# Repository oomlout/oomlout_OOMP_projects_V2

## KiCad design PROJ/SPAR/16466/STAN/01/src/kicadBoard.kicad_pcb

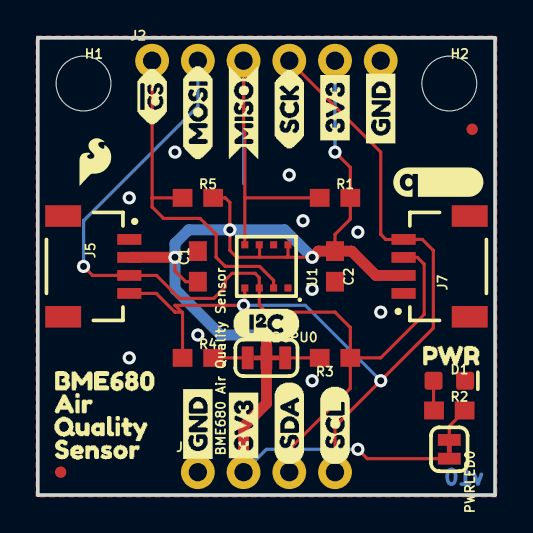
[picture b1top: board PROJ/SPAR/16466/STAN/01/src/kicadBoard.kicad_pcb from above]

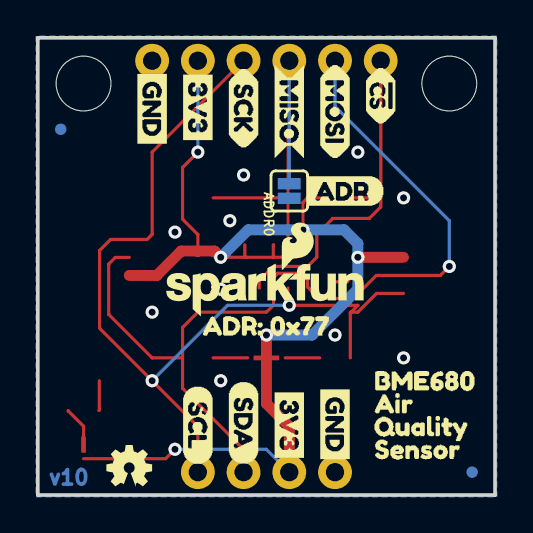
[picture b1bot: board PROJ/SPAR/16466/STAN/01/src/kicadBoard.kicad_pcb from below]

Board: 2 copper layers, 25.4 x 25.4 mm, 60 parts (21 on the bottom side), 10 nets.

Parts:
ADDR0: JUMPER-SMT_2_NO_SILK; SMT-JUMPER_2_NO_SILK
C1, C2: 0.1uF; 0603
D1: RED; LED-0603
FD1, FD2, FD3, FD4: FIDUCIALUFIDUCIAL; FIDUCIAL-MICRO
FRAME1: FRAME-LETTER; CREATIVE_COMMONS
H1, H2: STAND-OFFTIGHT; STAND-OFF-TIGHT
I2CPU0: I2C PU; SMT-JUMPER_3_2-NC_TRACE_SILK
J1: I2C; 1X04_NO_SILK
J2: SPI; 1X06_NO_SILK
J5, J7: QWIIC; JST04_1MM_RA
LOGO1: OSHW-LOGOMINI; OSHW-LOGO-MINI
LOGO2: SFE_LOGO_NAME_FLAME.1_INCH; SFE_LOGO_NAME_FLAME_.1
LOGO3: REVISION
LOGO4: SFE_LOGO_FLAME.1_INCH; SFE_LOGO_FLAME_.1
PWRLED0: JUMPER-SMT_2_NC_TRACE_SILK; SMT-JUMPER_2_NC_TRACE_SILK
R1, R3, R4, R5: 4.7k; 0603@1
R2: 1k; 0603
U1: BME680 Air Quality Sensor; LGA3.0X3.0
U$1, U$2: MISO_O
U$3, U$4: !CS_I
U$5, U$6: MOSI_I
U$7, U$8: SCK_I
U$9, U$10, U$16, U$17: 3V3_P
U$11, U$12, U$13, U$14: GND_P
U$15: I2C
U$18, U$19: SDA_IO
U$20, U$21: SCL_IO
U$22, U$26: BME6800
U$23, U$27: AIR1
U$24, U$28: QUALITY2
U$25, U$29: SENSOR3
U$30: ADR4
U$32: QWIIC_5MM
U$33: ADR#_0X770
U$34: PWR_TO

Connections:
3.3V: C1.1, C2.1, I2CPU0.2, J1.2, J2.5, J5.2, J7.2, PWRLED0.2, R1.2, R5.2, U1.6, U1.8
GND: ADDR0.1, C1.2, C2.2, D1.C, J1.1, J2.6, J5.1, J7.1, U1.1, U1.7
unnamed: PWRLED0.1, R2.2
unnamed: D1.A, R2.1
unnamed: I2CPU0.3, R3.2
unnamed: I2CPU0.1, R4.2
SCK/SCL: J1.4, J2.4, J5.4, J7.4, R4.1, U1.4
SDI/SDA: J1.3, J2.2, J5.3, J7.3, R3.1, U1.3
SDO/ADR: ADDR0.2, J2.3, R1.1, U1.5
~CS: J2.1, R5.1, U1.2

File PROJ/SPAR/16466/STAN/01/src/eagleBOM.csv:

"Part";"Value";"Device";"Package";"Description";"DESIGNER";"PROD_ID";"REV";"VALUE";
"ADDR";"JUMPER-SMT_2_NO_SILK";"JUMPER-SMT_2_NO_SILK";"SMT-JUMPER_2_NO_SILK";"Normally open jumper";"";"";"";"";
"C1";"0.1uF";"0.1UF-0603-100V-10%";"0603";"0.1µF ceramic capacitors";"";"CAP-08390";"";"0.1uF";
"C2";"0.1uF";"0.1UF-0603-100V-10%";"0603";"0.1µF ceramic capacitors";"";"CAP-08390";"";"0.1uF";
"D1";"RED";"LED-RED0603";"LED-0603";"Red SMD LED";"";"DIO-00819";"";"RED";
"FD1";"FIDUCIALUFIDUCIAL";"FIDUCIALUFIDUCIAL";"FIDUCIAL-MICRO";"Fiducial Alignment Points";"";"";"";"";
"FD2";"FIDUCIALUFIDUCIAL";"FIDUCIALUFIDUCIAL";"FIDUCIAL-MICRO";"Fiducial Alignment Points";"";"";"";"";
"FD3";"FIDUCIALUFIDUCIAL";"FIDUCIALUFIDUCIAL";"FIDUCIAL-MICRO";"Fiducial Alignment Points";"";"";"";"";
"FD4";"FIDUCIALUFIDUCIAL";"FIDUCIALUFIDUCIAL";"FIDUCIAL-MICRO";"Fiducial Alignment Points";"";"";"";"";
"FRAME1";"FRAME-LETTER";"FRAME-LETTER";"CREATIVE_COMMONS";"Schematic Frame - Letter";"";"";"";"";
"H1";"STAND-OFFTIGHT";"STAND-OFFTIGHT";"STAND-OFF-TIGHT";"Stand Off";"";"";"";"";
"H2";"STAND-OFFTIGHT";"STAND-OFFTIGHT";"STAND-OFF-TIGHT";"Stand Off";"";"";"";"";
"I2CPU";"I2C PU";"JUMPER-SMT_3_2-NC_TRACE_SILK";"SMT-JUMPER_3_2-NC_TRACE_SILK";"Normally closed trace jumper (2 of 2 connections)";"";"";"";"";
"J1";"I2C";"CONN_041X04_NO_SILK";"1X04_NO_SILK";"Multi connection point. Often used as Generic Header-pin footprint for 0.1 inch spaced/style header connections";"";"CONN-09696";"";"";
"J2";"SPI";"CONN_06NO_SILK_FEMALE_PTH";"1X06_NO_SILK";"Multi connection point. Often used as Generic Header-pin footprint for 0.1 inch spaced/style header connections";"";"CONN-08437";"";"";
"J5";"QWIIC";"QWIIC_CONNECTORJS-1MM";"JST04_1MM_RA";"SparkFun I2C Standard Qwiic Connector";"";"CONN-13694";"";"QWIIC_RIGHT_ANGLE";
"J7";"QWIIC";"QWIIC_CONNECTORJS-1MM";"JST04_1MM_RA";"SparkFun I2C Standard Qwiic Connector";"";"CONN-13694";"";"QWIIC_RIGHT_ANGLE";
"LOGO1";"OSHW-LOGOMINI";"OSHW-LOGOMINI";"OSHW-LOGO-MINI";"Open-Source Hardware (OSHW) Logo";"";"";"";"";
"LOGO2";"SFE_LOGO_NAME_FLAME.1_INCH";"SFE_LOGO_NAME_FLAME.1_INCH";"SFE_LOGO_NAME_FLAME_.1";"SparkFun Font Logo w/ Flame";"";"";"";"";
"LOGO3";"REVISION";"REVISION";"REVISION";""Revision By" Text";"";"";"";"";
"LOGO4";"SFE_LOGO_FLAME.1_INCH";"SFE_LOGO_FLAME.1_INCH";"SFE_LOGO_FLAME_.1";"SparkFun Flame Logo";"";"";"";"";
"PWRLED";"JUMPER-SMT_2_NC_TRACE_SILK";"JUMPER-SMT_2_NC_TRACE_SILK";"SMT-JUMPER_2_NC_TRACE_SILK";"Normally closed trace jumper";"";"";"";"";
"R1";"4.7k";"4.7KOHM-0603-1/10W-1%";"0603@1";"4.7kΩ resistor";"";"RES-07857";"";"4.7k";
"R2";"1k";"1KOHM-0603-1/10W-1%";"0603";"1kΩ resistor";"";"RES-07856";"";"1k";
"R3";"4.7k";"4.7KOHM-0603-1/10W-1%";"0603@1";"4.7kΩ resistor";"";"RES-07857";"";"4.7k";
"R4";"4.7k";"4.7KOHM-0603-1/10W-1%";"0603@1";"4.7kΩ resistor";"";"RES-07857";"";"4.7k";
"R5";"4.7k";"4.7KOHM-0603-1/10W-1%";"0603@1";"4.7kΩ resistor";"";"RES-07857";"";"4.7k";
"U1";"BME680 Air Quality Sensor";"BME680-LGA";"LGA3.0X3.0";"Bosch BME680 &ndash; Combined Humidity and Pressure Sensor";"";"IC-14656";"";"BME680";

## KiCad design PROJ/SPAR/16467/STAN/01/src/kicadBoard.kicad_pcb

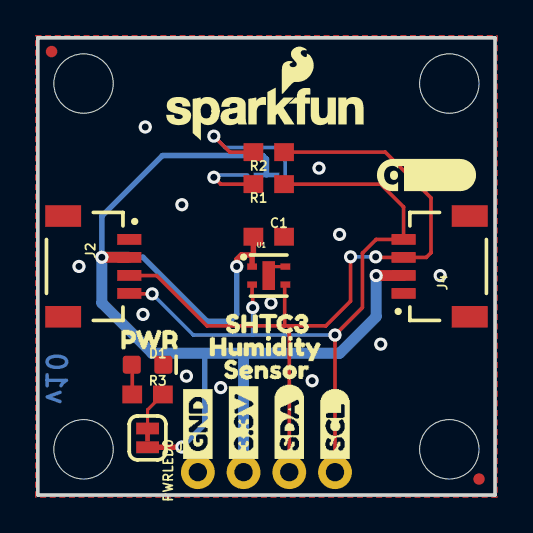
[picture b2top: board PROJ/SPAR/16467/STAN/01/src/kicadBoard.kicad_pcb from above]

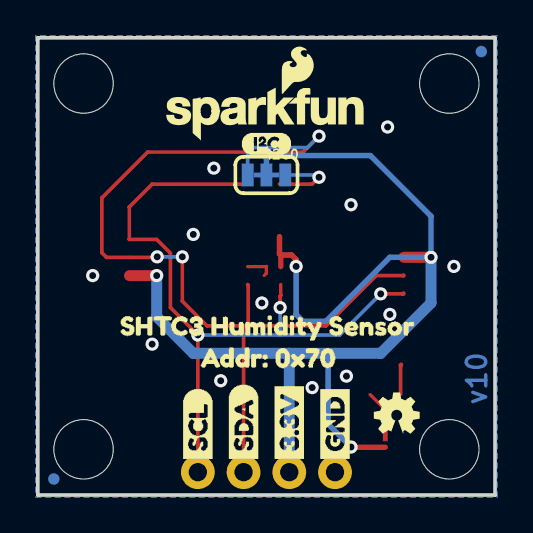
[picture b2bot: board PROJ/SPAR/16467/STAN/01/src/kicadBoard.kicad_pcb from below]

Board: 2 copper layers, 25.4 x 25.4 mm, 40 parts (12 on the bottom side), 8 nets.

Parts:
C1: 0.1uF; 0603
D1: RED; LED-0603
FRAME1: FRAME-LETTER; CREATIVE_COMMONS
I2C0: JUMPER-SMT_3_2-NC_TRACE_SILK; SMT-JUMPER_3_2-NC_TRACE_SILK
J1: 1X04_NO_SILK
J2, J4: QWIIC_RIGHT_ANGLE; JST04_1MM_RA
JP1, JP2, JP5, JP6: FIDUCIALUFIDUCIAL; MICRO-FIDUCIAL
JP3, JP4, JP7, JP8: STAND-OFF
LOGO1: OSHW-LOGOMINI; OSHW-LOGO-MINI
LOGO2, LOGO3: SFE_LOGO_NAME_FLAME.1_INCH; SFE_LOGO_NAME_FLAME_.1
LOGO4: REVISION
PWRLED0: JUMPER-SMT_2_NC_TRACE_SILK; SMT-JUMPER_2_NC_TRACE_SILK
R1, R2: 2.2k; 0603
R3: 1k; 0603
U1: SHTC3
U$1: ADDR#_0X700
U$2: PWR_TO
U$3, U$22: GND1
U$4, U$21: 3#3V2
U$5, U$27: SDA8
U$6, U$26: SCL9
U$7: SHTC3_HUMIDITY_SENSOR2
U$8: _SHTC31
U$9: I_SUPER2_C-()-03
U$10: HUMIDITY2
U$11: QWIIC_5.5MM
U$12: SENSOR0

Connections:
3.3V: C1.1, I2C0.2, J1.2, J2.2, J4.2, PWRLED0.2, U1.1
GND: C1.2, D1.C, J1.1, J2.1, J4.1, U1.4, U1.5
unnamed: I2C0.3, R1.2
unnamed: I2C0.1, R2.2
unnamed: D1.A, R3.1
unnamed: PWRLED0.1, R3.2
SCL: J1.4, J2.4, J4.4, R1.1, U1.2
SDA: J1.3, J2.3, J4.3, R2.1, U1.3

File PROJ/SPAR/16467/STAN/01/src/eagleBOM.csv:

"Part";"Value";"Device";"Package";"Description";"DESIGNER";"PROD_ID";"REV";"VALUE";
"C1";"0.1uF";"0.1UF-0603-25V-(+80/-20%)";"0603";"0.1µF ceramic capacitors";"";"CAP-00810";"";"0.1uF";
"D1";"RED";"LED-RED0603";"LED-0603";"Red SMD LED";"";"DIO-00819";"";"RED";
"FRAME1";"FRAME-LETTER";"FRAME-LETTER";"CREATIVE_COMMONS";"Schematic Frame - Letter";"";"";"";"";
"I2C";"JUMPER-SMT_3_2-NC_TRACE_SILK";"JUMPER-SMT_3_2-NC_TRACE_SILK";"SMT-JUMPER_3_2-NC_TRACE_SILK";"Normally closed trace jumper (2 of 2 connections)";"";"";"";"";
"J1";"";"CONN_041X04_NO_SILK";"1X04_NO_SILK";"Multi connection point. Often used as Generic Header-pin footprint for 0.1 inch spaced/style header connections";"";"CONN-09696";"";"";
"J2";"QWIIC_RIGHT_ANGLE";"QWIIC_CONNECTORJS-1MM";"JST04_1MM_RA";"SparkFun I2C Standard Qwiic Connector";"";"CONN-13694";"";"QWIIC_RIGHT_ANGLE";
"J4";"QWIIC_RIGHT_ANGLE";"QWIIC_CONNECTORJS-1MM";"JST04_1MM_RA";"SparkFun I2C Standard Qwiic Connector";"";"CONN-13694";"";"QWIIC_RIGHT_ANGLE";
"JP1";"FIDUCIALUFIDUCIAL";"FIDUCIALUFIDUCIAL";"MICRO-FIDUCIAL";"Fiducial Alignment Points";"";"";"";"";
"JP2";"FIDUCIALUFIDUCIAL";"FIDUCIALUFIDUCIAL";"MICRO-FIDUCIAL";"Fiducial Alignment Points";"";"";"";"";
"JP3";"STAND-OFF";"STAND-OFF";"STAND-OFF";"Stand Off";"";"";"";"";
"JP4";"STAND-OFF";"STAND-OFF";"STAND-OFF";"Stand Off";"";"";"";"";
"JP5";"FIDUCIALUFIDUCIAL";"FIDUCIALUFIDUCIAL";"MICRO-FIDUCIAL";"Fiducial Alignment Points";"";"";"";"";
"JP6";"FIDUCIALUFIDUCIAL";"FIDUCIALUFIDUCIAL";"MICRO-FIDUCIAL";"Fiducial Alignment Points";"";"";"";"";
"JP7";"STAND-OFF";"STAND-OFF";"STAND-OFF";"Stand Off";"";"";"";"";
"JP8";"STAND-OFF";"STAND-OFF";"STAND-OFF";"Stand Off";"";"";"";"";
"LOGO1";"OSHW-LOGOMINI";"OSHW-LOGOMINI";"OSHW-LOGO-MINI";"Open-Source Hardware (OSHW) Logo";"";"";"";"";
"LOGO2";"SFE_LOGO_NAME_FLAME.1_INCH";"SFE_LOGO_NAME_FLAME.1_INCH";"SFE_LOGO_NAME_FLAME_.1";"SparkFun Font Logo w/ Flame";"";"";"";"";
"LOGO3";"SFE_LOGO_NAME_FLAME.1_INCH";"SFE_LOGO_NAME_FLAME.1_INCH";"SFE_LOGO_NAME_FLAME_.1";"SparkFun Font Logo w/ Flame";"";"";"";"";
"LOGO4";"REVISION";"REVISION";"REVISION";""Revision By" Text";"";"";"";"";
"PWRLED";"JUMPER-SMT_2_NC_TRACE_SILK";"JUMPER-SMT_2_NC_TRACE_SILK";"SMT-JUMPER_2_NC_TRACE_SILK";"Normally closed trace jumper";"";"";"";"";
"R1";"2.2k";"2.2KOHM-0603-1/10W-1%";"0603";"2.2kΩ resistor";"";"RES-08272";"";"2.2k";
"R2";"2.2k";"2.2KOHM-0603-1/10W-1%";"0603";"2.2kΩ resistor";"";"RES-08272";"";"2.2k";
"R3";"1k";"1KOHM-0603-1/10W-1%";"0603";"1kΩ resistor";"";"RES-07856";"";"1k";
"U1";"SHTC3";"SHTC3";"SHTC3";"Sensirion SHTC3 Humidity Sensor";"";"IC-14840";"";"SHTC3";

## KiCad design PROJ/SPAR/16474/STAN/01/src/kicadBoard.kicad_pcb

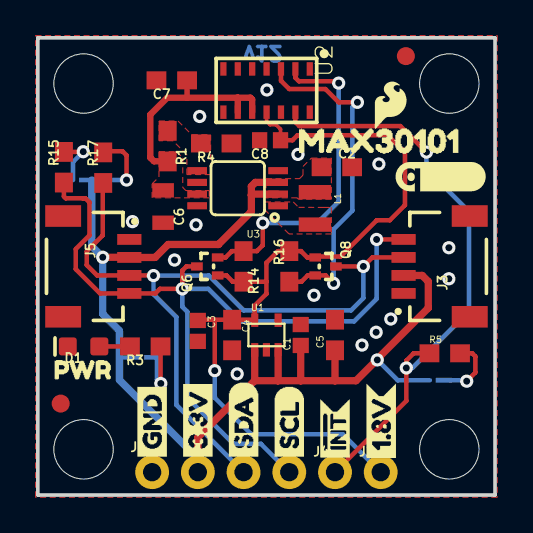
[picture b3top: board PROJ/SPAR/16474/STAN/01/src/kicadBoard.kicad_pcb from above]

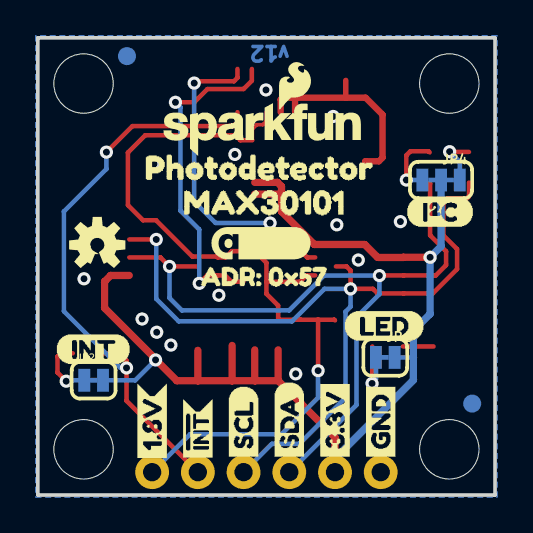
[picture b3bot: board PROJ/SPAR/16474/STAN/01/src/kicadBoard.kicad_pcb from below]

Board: 2 copper layers, 25.4 x 25.4 mm, 65 parts (20 on the bottom side), 16 nets.

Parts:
C1, C3, C8: 0.1uF; 0402
C2, C4, C5, C7: 10uF; 0603
C6: 22uF; 0805
D1: RED; LED-0603
FID1, FID2, FID3, FID4: FIDUCIAL1X2; FIDUCIAL-1X2
FRAME1: FRAME-LETTER; CREATIVE_COMMONS
J1: PTH; 1X04_NO_SILK
J2, J4: 1X01_NO_SILK
J3, J5: QWIIC_RA; JST04_1MM_RA
JP1: LED; SMT-JUMPER_2_NC_TRACE_SILK
JP2: INT; SMT-JUMPER_2_NC_TRACE_SILK
JP4: I2C PU; SMT-JUMPER_3_2-NC_TRACE_SILK
L1: 2.2μH; 0806
LOGO1: SFE_LOGO_NAME_FLAME.1_INCH; SFE_LOGO_NAME_FLAME_.1
LOGO2: OSHW-LOGOS; OSHW-LOGO-S
LOGO3: QWIIC_LOGO_5MM; QWIIC_5MM
LOGO4: SFE_LOGO_FLAME.1_INCH; SFE_LOGO_FLAME_.1
Q6, Q8: 20V/0.2A/8MHz/1.2Ω/1Vth; SOT-416FL
R1: 750K; 0603
R3: 1k; 0603
R4: 100k; 0603
R5: 4.7k; 0603
R14, R15, R16, R17: 2.2k; 0603
STANDOFF1, STANDOFF2, STANDOFF3, STANDOFF4: STAND-OFF
U1: 1.8V/100mA; SC70
U2: MAX30101EFD; 14_PIN_OESIP
U3: PAM2401; MSOP8
U$1: PHOTODETECTOR3
U$3, U$11: INT#-[_-04
U$4, U$24: MAX301010
U$7: INT-()-04
U$8: LED0
U$9, U$12: SCL-[)
U$10, U$23: GND-04
U$13, U$14: SDA-[)
U$15: ADR#_0X570
U$16: QWIIC_5.5MM
U$19, U$22: 3.3V
U$20, U$27: 1#8V0
U$21: I_SUPER2_C-()-04
U$26: PWR_TO

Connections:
1.8V: C3.1, C4.1, C8.1, J2.1, Q6.1, Q8.1, R14.2, R16.2, U1.5, U2.P11
3.3V: C1.1, C2.1, C5.1, J1.2, J3.2, J5.2, JP1.2, JP2.2, JP4.2, L1.1, U1.1, U1.3, U3.2, U3.3
5V: C6.1, C7.1, R1.2, U2.P9, U2.P10, U3.7
GND: C1.2, C2.2, C3.2, C4.2, C5.2, C6.2, C7.2, C8.2, D1.C, J1.1, J3.1, J5.1, R4.1, U1.2, U1.4, U2.P4, U2.P12, U3.4, U3.8
LV_SCL: Q6.2, R14.1, U2.P2
LV_SDA: Q8.2, R16.1, U2.P3
unnamed: JP2.1, R5.2
unnamed: R1.1, R4.2, U3.5
unnamed: L1.2, U3.1
unnamed: D1.A, R3.2
unnamed: JP4.3, R15.2
unnamed: JP4.1, R17.2
unnamed: JP1.1, R3.1
SCL: J1.4, J3.4, J5.4, Q6.3, R15.1
SDA: J1.3, J3.3, J5.3, Q8.3, R17.1
~INT: J4.1, R5.1, U2.P13

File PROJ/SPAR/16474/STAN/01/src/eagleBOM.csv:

"Part";"Value";"Device";"Package";"Description";"DESIGNER";"PROD_ID";"REV";"VALUE";
"C1";"0.1uF";"0.1UF-0402-16V-10%";"0402";"0.1µF ceramic capacitors";"";"CAP-12416";"";"0.1uF";
"C2";"10uF";"10UF-0603-6.3V-20%";"0603";"10.0µF ceramic capacitors";"";"CAP-11015";"";"10uF";
"C3";"0.1uF";"0.1UF-0402-16V-10%";"0402";"0.1µF ceramic capacitors";"";"CAP-12416";"";"0.1uF";
"C4";"10uF";"10UF-0603-6.3V-20%";"0603";"10.0µF ceramic capacitors";"";"CAP-11015";"";"10uF";
"C5";"10uF";"10UF-0603-6.3V-20%";"0603";"10.0µF ceramic capacitors";"";"CAP-11015";"";"10uF";
"C6";"22uF";"22UF-0805-6.3V-20%";"0805";"22µF ceramic capacitors";"";"CAP-08402";"";"22uF";
"C7";"10uF";"10UF-0603-6.3V-20%";"0603";"10.0µF ceramic capacitors";"";"CAP-11015";"";"10uF";
"C8";"0.1uF";"0.1UF-0402-16V-10%";"0402";"0.1µF ceramic capacitors";"";"CAP-12416";"";"0.1uF";
"D1";"RED";"LED-RED0603";"LED-0603";"Red SMD LED";"";"DIO-00819";"";"RED";
"FID1";"FIDUCIAL1X2";"FIDUCIAL1X2";"FIDUCIAL-1X2";"Fiducial Alignment Points";"";"";"";"";
"FID2";"FIDUCIAL1X2";"FIDUCIAL1X2";"FIDUCIAL-1X2";"Fiducial Alignment Points";"";"";"";"";
"FID3";"FIDUCIAL1X2";"FIDUCIAL1X2";"FIDUCIAL-1X2";"Fiducial Alignment Points";"";"";"";"";
"FID4";"FIDUCIAL1X2";"FIDUCIAL1X2";"FIDUCIAL-1X2";"Fiducial Alignment Points";"";"";"";"";
"FRAME1";"FRAME-LETTER";"FRAME-LETTER";"CREATIVE_COMMONS";"Schematic Frame - Letter";"";"";"";"";
"J1";"PTH";"I2C_STANDARD_NO_SILK";"1X04_NO_SILK";"SparkFun I2C Standard Pinout Header";"";"";"";"";
"J2";"";"CONN_01PTH_NO_SILK_YES_STOP";"1X01_NO_SILK";"Single connection point. Often used as Generic Header-pin footprint for 0.1 inch spaced/style header connections";"";"";"";"";
"J3";"QWIIC_RA";"QWIIC_CONNECTORJS-1MM";"JST04_1MM_RA";"SparkFun I2C Standard Qwiic Connector";"";"CONN-13694";"";"QWIIC_RIGHT_ANGLE";
"J4";"";"CONN_01PTH_NO_SILK_YES_STOP";"1X01_NO_SILK";"Single connection point. Often used as Generic Header-pin footprint for 0.1 inch spaced/style header connections";"";"";"";"";
"J5";"QWIIC_RA";"QWIIC_CONNECTORJS-1MM";"JST04_1MM_RA";"SparkFun I2C Standard Qwiic Connector";"";"CONN-13694";"";"QWIIC_RIGHT_ANGLE";
"JP1";"LED";"JUMPER-SMT_2_NC_TRACE_SILK";"SMT-JUMPER_2_NC_TRACE_SILK";"Normally closed trace jumper";"";"";"";"";
"JP2";"INT";"JUMPER-SMT_2_NC_TRACE_SILK";"SMT-JUMPER_2_NC_TRACE_SILK";"Normally closed trace jumper";"";"";"";"";
"JP4";"I2C PU";"JUMPER-SMT_3_2-NC_TRACE_SILK";"SMT-JUMPER_3_2-NC_TRACE_SILK";"Normally closed trace jumper (2 of 2 connections)";"";"";"";"";
"L1";"2.2μH";"2.2μH_SHIELDED_INDUCTOR";"0806";"Murata 2.2uH Inductor";"";"NDUC-14257";"";"";
"LOGO1";"SFE_LOGO_NAME_FLAME.1_INCH";"SFE_LOGO_NAME_FLAME.1_INCH";"SFE_LOGO_NAME_FLAME_.1";"SparkFun Font Logo w/ Flame";"";"";"";"";
"LOGO2";"OSHW-LOGOS";"OSHW-LOGOS";"OSHW-LOGO-S";"Open-Source Hardware (OSHW) Logo";"";"";"";"";
"LOGO3";"QWIIC_LOGO_5MM";"QWIIC_LOGO_5MM";"QWIIC_5MM";"Qwiic Logos for placement on schematic and PCB. The 5.5mm silk logo is best for placing next to Qwiic connector.";"";"";"";"";
"LOGO4";"SFE_LOGO_FLAME.1_INCH";"SFE_LOGO_FLAME.1_INCH";"SFE_LOGO_FLAME_.1";"SparkFun Flame Logo";"";"";"";"";
"Q6";"20V/0.2A/8MHz/1.2Ω/1Vth";"MOSFET-NCH-RE1C00UNTL";"SOT-416FL";"N-channel MOSFETs";"";"TRANS-14399";"";"20V/0.2A/8MHz/1.2Ω/1Vth";
"Q8";"20V/0.2A/8MHz/1.2Ω/1Vth";"MOSFET-NCH-RE1C00UNTL";"SOT-416FL";"N-channel MOSFETs";"";"TRANS-14399";"";"20V/0.2A/8MHz/1.2Ω/1Vth";
"R1";"750K";"750KOHM-0603-1/10W-1%";"0603";"750Ω resistor";"";"RES-13768";"";"750K";
"R3";"1k";"1KOHM-0603-1/10W-1%";"0603";"1kΩ resistor";"";"RES-07856";"";"1k";
"R4";"100k";"100KOHM-0603-1/10W-1%";"0603";"100kΩ resistor";"";"RES-07828";"";"100k";
"R5";"4.7k";"4.7KOHM-0603-1/10W-1%";"0603";"4.7kΩ resistor";"";"RES-07857";"";"4.7k";
"R14";"2.2k";"2.2KOHM-0603-1/10W-1%";"0603";"2.2kΩ resistor";"";"RES-08272";"";"2.2k";
"R15";"2.2k";"2.2KOHM-0603-1/10W-1%";"0603";"2.2kΩ resistor";"";"RES-08272";"";"2.2k";
"R16";"2.2k";"2.2KOHM-0603-1/10W-1%";"0603";"2.2kΩ resistor";"";"RES-08272";"";"2.2k";
"R17";"2.2k";"2.2KOHM-0603-1/10W-1%";"0603";"2.2kΩ resistor";"";"RES-08272";"";"2.2k";
"STANDOFF1";"STAND-OFF";"STAND-OFF";"STAND-OFF";"#4 Stand Off";"";"";"";"";
"STANDOFF2";"STAND-OFF";"STAND-OFF";"STAND-OFF";"#4 Stand Off";"";"";"";"";
"STANDOFF3";"STAND-OFF";"STAND-OFF";"STAND-OFF";"#4 Stand Off";"";"";"";"";
"STANDOFF4";"STAND-OFF";"STAND-OFF";"STAND-OFF";"#4 Stand Off";"";"";"";"";
"U1";"1.8V/100mA";"V_REG_SP62141.8V";"SC70";"";"";"VREG-08428";"";"1.8V/100mA";
"U2";"MAX30101EFD";"MAX30101EFD";"14_PIN_OESIP";"MAX30101 High-Sensitivity Pulse Oximeter and";"";"IC-14270";"";"";
"U3";"PAM2401";"PAM2401";"MSOP8";"PAM2401 - Boost PMIC";"";"IC-13769";"";"PAM2401";

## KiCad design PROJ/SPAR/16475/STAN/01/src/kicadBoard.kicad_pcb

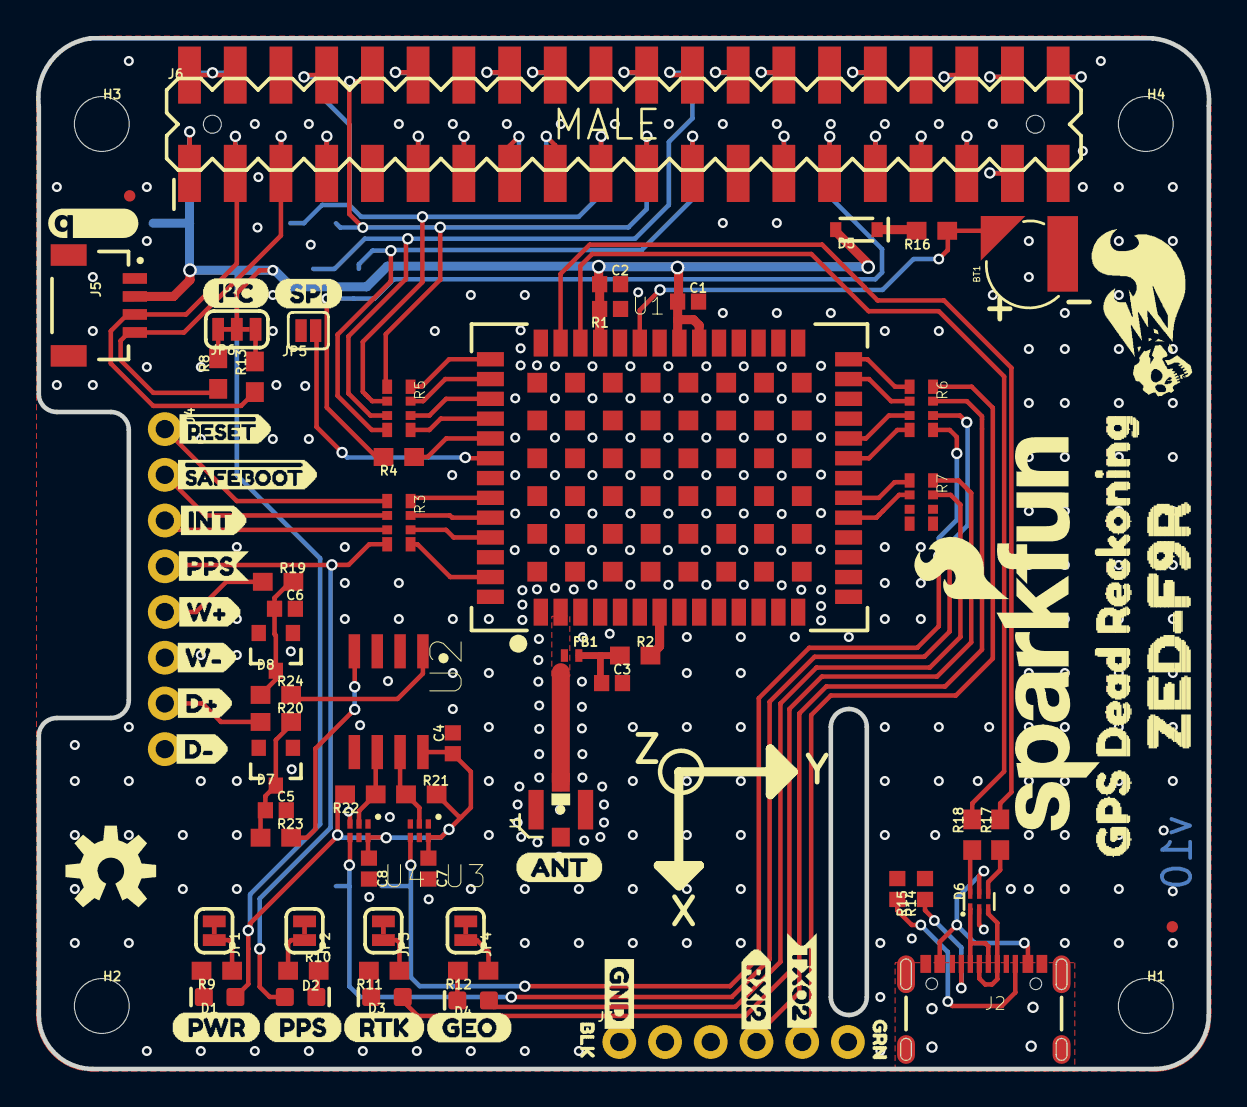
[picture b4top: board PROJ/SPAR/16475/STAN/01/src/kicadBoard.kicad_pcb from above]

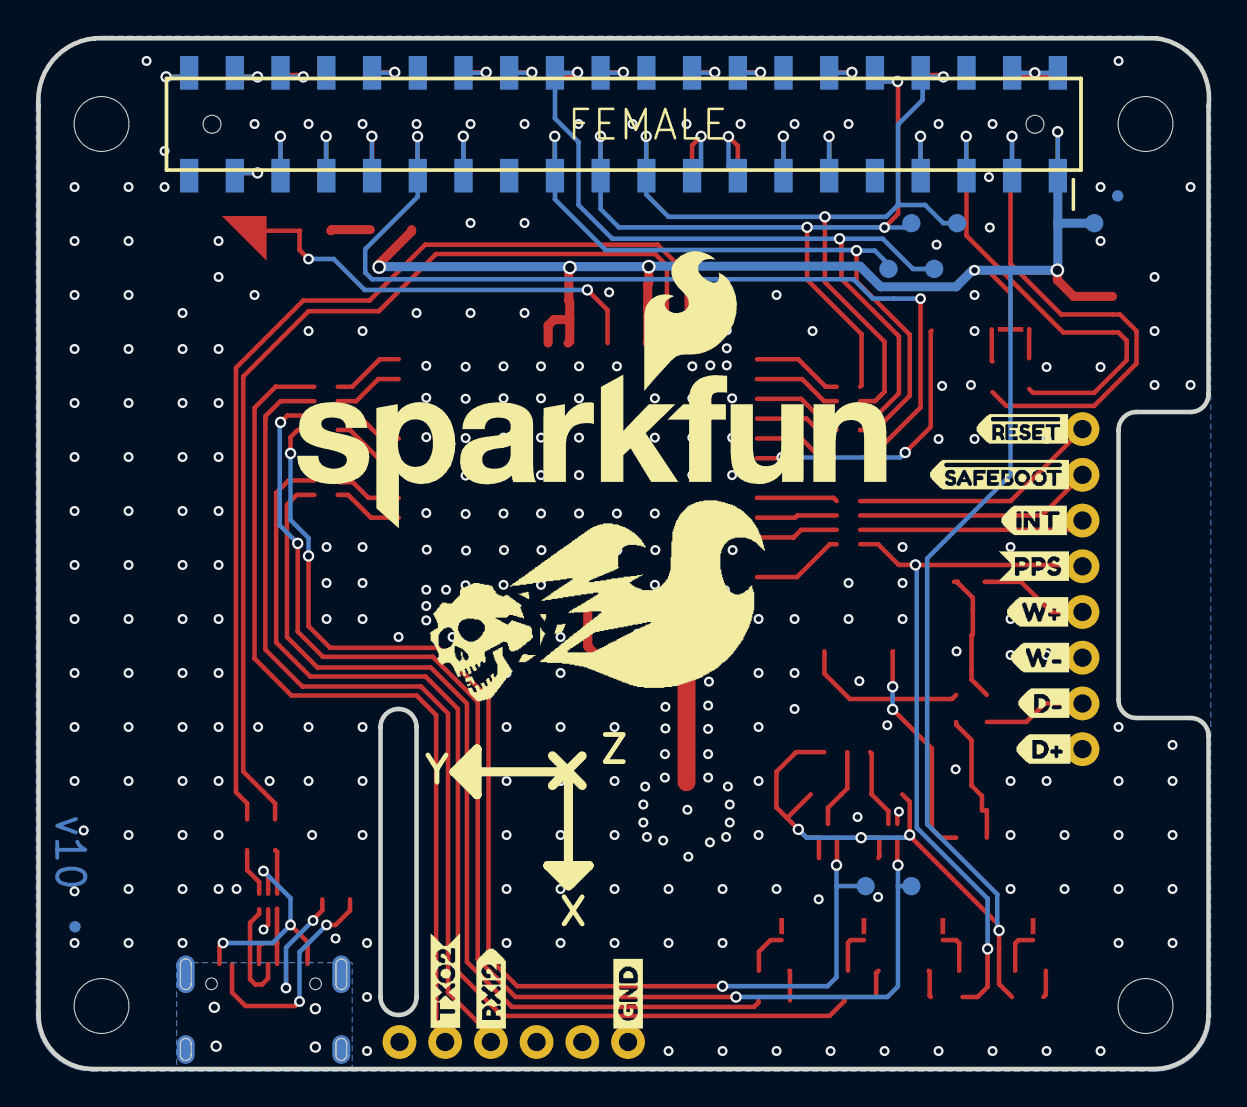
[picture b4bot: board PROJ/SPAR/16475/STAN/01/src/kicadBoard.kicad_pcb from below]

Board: 2 copper layers, 65.0 x 57.3 mm, 113 parts (22 on the bottom side), 88 nets.

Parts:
BT1: ML414H_IV01E_BATTERY; ML414H_IV01E
C1, C2: 1.0uF; 0402
C3: 47pF; 0402
C4, C7, C8: 0.1uF; 0402
C5, C6: 1nF; 0402
D1: RED; LED-0603
D2, D3, D4: BLUE; LED-0603
D5: 0.5A/40V/420mV; SOD-323
D6: PRTR5V0U2F; SOT886
D7, D8: 15V; SOT23-3
FB1: 120NH; 0402_MURATA
FD1, FD2, FD3, FD4: FIDUCIALUFIDUCIAL; FIDUCIAL-MICRO
FRAME1: FRAME-LEDGER; CREATIVE_COMMONS
H1, H2, H3, H4: STAND-OFFTIGHT; STAND-OFF-TIGHT
J1: U.FL
J2: USB-C-16P
J3: 1X06_NO_SILK
J4: 1X08_NO_SILK
J5: QWIIC_RIGHT_ANGLE; JST04_1MM_RA
J6: RASPBERRYPI-40-PIN-GPIO_SMD_STACK_NOHOLES_NOREF; RASPBERRY_PI_HAT_40_PIN_SMD_STACKABLE_NOHOLES_NOREF
JP1, JP2, JP3, JP4: JUMPER-SMT_2_NC_TRACE_SILK; SMT-JUMPER_2_NC_TRACE_SILK
JP5: JUMPER-SMT_2_NO_SILK; SMT-JUMPER_2_NO_SILK
JP6: JUMPER-SMT_3_2-NC_TRACE_SILK; SMT-JUMPER_3_2-NC_TRACE_SILK
LOGO1: QWIIC_LOGO_5MM; QWIIC_5MM
LOGO2: OSHW-LOGOM; OSHW-LOGO-M
LOGO3: SFE_LOGO_NAME_FLAME.2_INCH; SFE_LOGO_NAME_FLAME_.2
R1: 100K; 0402
R2, R4: 33; 0603
R3, R5, R6, R7: 33; 1206_RA
R8, R13: 2.2k; 0603
R9, R10, R11, R12: 1k; 0603
R14, R15: 5.1k; 0402
R16, R19, R20: 3.3k; 0603
R17, R18: 27; 0603
R21, R22: 910; 0603
R23, R24: 470; 0603
TP1, TP2, TP3, TP4, TP5, TP6, TP7: TEST-POINT3X4; PAD.03X.04
U1: U-BLOX_ZED_F9R; UBLOX_ZED_F9R
U2: DUAL-OPTO_HCPL-073L; SOP_8-PIN
U3, U4: UHS_INVERTER_SCHMITT_TRIGGERSIP6; SIP6
U$1: INT1
U$2: PPS4
U$3: PPS6
U$4: PWR7
U$5: RTK5
U$6: RXI28
U$7: #RESET1
U$8: #RESET2
U$9: SFE_LOGO_NAME_FLAME_.3
U$10: TXO21
U$11: INT2
U$12: PPS1
U$13: #SAFEBOOT0
U$14: RXI26
U$15: #SAFEBOOT3
U$16: TXO25
U$17: BLK2
U$18, U$19: GND-04
U$20: I_SUPER2_C-()-04
U$21: ANT1
U$22, U$32: D#0
U$23, U$33: D#1
U$24: SPI0
U$25: GPS_DEAD_RECKONING0
U$26: ZED#F9R0
U$27, U$34: W#2
U$28, U$35: W#3
U$29: GEO0
U$30: GRN1
U$31, U$36: DEAD#RECKONING#GPS#BOARD#SILK#FINAL#JPG

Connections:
3.3V: C1.1, C2.1, C4.1, C7.1, C8.1, D1.A, D5.A, J5.2, J6.1, J6.1B, J6.17, J6.17B, JP6.2, R1.2, R21.2, R22.2, TP5.P$1, U1.P33, U1.P34, U1.P38, U2.P8, U3.P6, U4.P6
5V: J6.2, J6.2B, J6.4, J6.4B
CE1: J6.26, J6.26B
DIR+: J4.7, R20.1
DIR_IN: R23.2, U2.P4
DIR_OUT: R6.P6, TP7.P$1, U4.P4
DIR_SCHMITT: R22.1, U2.P6, U4.P2
DMINUS: R18.2, U1.P39
DPLUS: R17.2, U1.P40
D_SEL: JP5.1, U1.P47
GEOF_STAT: D4.A, R7.P7
GND: BT1.-, C1.2, C2.2, C3.2, C4.2, C5.2, C6.2, C7.2, C8.2, D6.2, D7.1, D8.1, J1.1, J1.2, J2.GND, J2.GND2, J3.1, J4.6, J4.8, J5.1, J6.6, J6.6B, J6.9, J6.9B, J6.14, J6.14B, J6.20, J6.20B, J6.25, J6.25B, J6.30, J6.30B, J6.34, J6.34B, J6.39, J6.39B, JP1.1, JP2.1, JP3.1, JP4.1, JP5.2, R1.1, R14.1, R15.1, U1.G1, U1.G2, U1.G3, U1.G4, U1.G5, U1.G6, U1.G7, U1.G8, U1.G9, U1.G10, U1.G11, U1.G12, U1.G13, U1.G14, U1.G15, U1.G16, U1.G17, U1.G18, U1.G19, U1.G20, U1.G21, U1.G22, U1.G23, U1.G24, U1.G25, U1.G26, U1.G27, U1.G28, U1.G29, U1.G30, U1.G31, U1.G32, U1.G33, U1.G34, U1.G35, U1.G36, U1.G37, U1.G38, U1.G39, U1.G40, U1.G41, U1.G42, U1.G43, U1.G44, U1.G45, U1.G46, U1.G47, U1.G48, U1.P1, U1.P3, U1.P12, U1.P14, U1.P32, U1.P37, U1.P41, U1.P48, U2.P2, U2.P3, U2.P5, U3.P3, U4.P3
GP4: J6.7, J6.7B
GP6: J6.31, J6.31B
GP12: J6.32, J6.32B
GP13: J6.33, J6.33B
GP16: J6.36, J6.36B
GP17: J6.11, J6.11B
GP18: J6.12, J6.12B
GP19: J6.35, J6.35B
GP20: J6.38, J6.38B
GP21: J6.40, J6.40B
GP22: J6.15, J6.15B
GP23: J6.16, J6.16B
GP24: J6.18, J6.18B
GP25: J6.22, J6.22B
GP26: J6.37, J6.37B
GP27: J6.13, J6.13B
ID_SC: J6.28, J6.28B
ID_SD: J6.27, J6.27B
INT: J4.3, R3.P3
unnamed: JP6.1, R13.2
unnamed: D5.C, R16.2
unnamed: JP6.3, R8.2
unnamed: D1.C, R9.2
unnamed: C3.1, FB1.P2, R2.1
unnamed: D6.6, R18.1
unnamed: D6.4, R17.1
unnamed: JP1.2, R9.1
unnamed: D6.3, J2.A6, J2.B6
unnamed: D6.5, J2.VBUS1, J2.VBUS2
unnamed: D6.1, J2.A7, J2.B7
unnamed: J2.B5, R14.2
unnamed: R3.P8, U1.P49
unnamed: R3.P6, U1.P51
unnamed: R5.P6, U1.P44
unnamed: JP4.2, R12.1
unnamed: D4.C, R12.2
unnamed: J2.A5, R15.2
unnamed: R5.P5, U1.P45
unnamed: R4.1, U1.P46
unnamed: R5.P8, U1.P42
unnamed: JP3.2, R11.1
unnamed: JP2.2, R10.1
unnamed: D2.C, R10.2
unnamed: D3.C, R11.2
unnamed: R5.P7, U1.P43
unnamed: C6.1, D8.3, R19.2, R24.1
unnamed: R7.P2, U1.P19
unnamed: R7.P1, U1.P20
unnamed: R3.P5, U1.P53
unnamed: R3.P7, U1.P50
unnamed: R6.P1, U1.P27
unnamed: R6.P2, U1.P26
unnamed: R6.P4, U1.P22
unnamed: R6.P3, U1.P23
unnamed: C5.1, D7.3, R20.2, R23.1
PPS: D2.A, J4.4, R3.P4
QWIIC_SCL: J5.4, J6.5, J6.5B, R8.1
QWIIC_SDA: J5.3, J6.3, J6.3B, R13.1
RF_IN: FB1.P1, J1.FEED, U1.P2
RTK_STAT: D3.A, R7.P8
RXI2: J3.4, R6.P7
RXI/MOSI: J6.8, J6.8B, J6.19, J6.19B, R5.P2, TP1.P$1
SCL/CLK: J6.23, J6.23B, R5.P4, TP3.P$1
SDA/~CS: J6.24, J6.24B, R5.P3, TP4.P$1
SHIELD: J2.SHLD1, J2.SHLD2, J2.SHLD3, J2.SHLD4, J2.SHLD5, J2.SHLD6, J2.SHLD7, J2.SHLD8
TXO2: J3.5, R6.P8
TXO/MISO: J6.10, J6.10B, J6.21, J6.21B, R5.P1, TP2.P$1
TX_READY: J6.29, J6.29B, R4.2
V_BATT: BT1.+, R16.1, U1.P36
V_RF: R2.2, U1.P7
WT+: J4.5, R19.1
WT_IN: R24.2, U2.P1
WT_OUT: R6.P5, TP6.P$1, U3.P4
WT_SCHMITT: R21.1, U2.P7, U3.P2
~RESET: J4.1, R3.P1
~SAFEBOOT: J4.2, R3.P2

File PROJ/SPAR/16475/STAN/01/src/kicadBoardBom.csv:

"Id";"Designator";"Package";"Quantity";"Designation";"Supplier and ref";
1;"C6,C5";"0402";2;"1nF";;;
2;"R17,R18";"0603";2;"27";;;
3;"H2,H4,H1,H3";"STAND-OFF-TIGHT";4;"STAND-OFFTIGHT";;;
4;"U2";"SOP_8-PIN";1;"DUAL-OPTO_HCPL-073L";;;
5;"C4,C8,C7";"0402";3;"0.1uF";;;
6;"BT1";"ML414H_IV01E";1;"ML414H_IV01E_BATTERY";;;
7;"D3,D2,D4";"LED-0603";3;"BLUE";;;
8;"R6,R3,R5,R7";"1206_RA";4;"33";;;
9;"U$23,U$33";"D#1";2;"";;;
10;"J5";"JST04_1MM_RA";1;"QWIIC_RIGHT_ANGLE";;;
11;"R20,R16,R19";"0603";3;"3.3k";;;
12;"U$25";"GPS_DEAD_RECKONING0";1;"";;;
13;"R11,R10,R9,R12";"0603";4;"1k";;;
14;"D8,D7";"SOT23-3";2;"15V";;;
15;"U1";"UBLOX_ZED_F9R";1;"U-BLOX_ZED_F9R";;;
16;"J2";"USB-C-16P";1;"";;;
17;"U$13";"#SAFEBOOT0";1;"";;;
18;"J3";"1X06_NO_SILK";1;"";;;
19;"U3,U4";"SIP6";2;"UHS_INVERTER_SCHMITT_TRIGGERSIP6";;;
20;"R13,R8";"0603";2;"2.2k";;;
21;"R14,R15";"0402";2;"5.1k";;;
22;"U$18,U$19";"GND-04";2;"";;;
23;"U$17";"BLK2";1;"";;;
24;"FB1";"0402_MURATA";1;"120NH";;;
25;"R22,R21";"0603";2;"910";;;
26;"LOGO3";"SFE_LOGO_NAME_FLAME_.2";1;"SFE_LOGO_NAME_FLAME.2_INCH";;;
27;"U$20";"I_SUPER2_C-()-04";1;"";;;
28;"R2,R4";"0603";2;"33";;;
29;"U$29";"GEO0";1;"";;;
30;"JP2,JP1,JP4,JP3";"SMT-JUMPER_2_NC_TRACE_SILK";4;"JUMPER-SMT_2_NC_TRACE_SILK";;;
31;"C1,C2";"0402";2;"1.0uF";;;
32;"U$31,U$36";"DEAD#RECKONING#GPS#BOARD#SILK#FINAL#JPG";2;"";;;
33;"D1";"LED-0603";1;"RED";;;
34;"U$24";"SPI0";1;"";;;
35;"JP6";"SMT-JUMPER_3_2-NC_TRACE_SILK";1;"JUMPER-SMT_3_2-NC_TRACE_SILK";;;
36;"U$7";"#RESET1";1;"";;;
37;"D5";"SOD-323";1;"0.5A/40V/420mV";;;
38;"U$27,U$34";"W#2";2;"";;;
39;"U$28,U$35";"W#3";2;"";;;
40;"U$2";"PPS4";1;"";;;
41;"U$3";"PPS6";1;"";;;
42;"LOGO2";"OSHW-LOGO-M";1;"OSHW-LOGOM";;;
43;"R1";"0402";1;"100K";;;
44;"U$6";"RXI28";1;"";;;
45;"J4";"1X08_NO_SILK";1;"";;;
46;"U$10";"TXO21";1;"";;;
47;"R23,R24";"0603";2;"470";;;
48;"LOGO1";"QWIIC_5MM";1;"QWIIC_LOGO_5MM";;;
49;"JP5";"SMT-JUMPER_2_NO_SILK";1;"JUMPER-SMT_2_NO_SILK";;;
50;"U$4";"PWR7";1;"";;;
51;"U$5";"RTK5";1;"";;;
52;"FD3,FD1,FD4,FD2";"FIDUCIAL-MICRO";4;"FIDUCIALUFIDUCIAL";;;
53;"U$26";"ZED#F9R0";1;"";;;
54;"U$22,U$32";"D#0";2;"";;;
55;"D6";"SOT886";1;"PRTR5V0U2F";;;
56;"U$1";"INT1";1;"";;;
57;"J6";"RASPBERRY_PI_HAT_40_PIN_SMD_STACKABLE_NOHOLES_NOREF";1;"RASPBERRYPI-40-PIN-GPIO_SMD_STACK_NOHOLES_NOREF";;;
58;"J1";"U.FL";1;"U.FL";;;
59;"U$21";"ANT1";1;"";;;
60;"U$30";"GRN1";1;"";;;
61;"C3";"0402";1;"47pF";;;
62;"FRAME1";"CREATIVE_COMMONS";1;"FRAME-LEDGER";;;
63;"TP7,TP3,TP5,TP4,TP1,TP2,TP6";"PAD.03X.04";7;"TEST-POINT3X4";;;
64;"U$8";"#RESET2";1;"";;;
65;"U$15";"#SAFEBOOT3";1;"";;;
66;"U$16";"TXO25";1;"";;;
67;"U$11";"INT2";1;"";;;
68;"U$12";"PPS1";1;"";;;
69;"U$9";"SFE_LOGO_NAME_FLAME_.3";1;"";;;
70;"U$14";"RXI26";1;"";;;

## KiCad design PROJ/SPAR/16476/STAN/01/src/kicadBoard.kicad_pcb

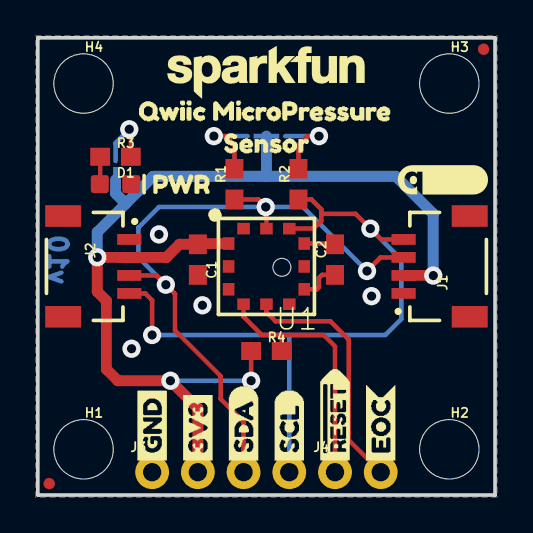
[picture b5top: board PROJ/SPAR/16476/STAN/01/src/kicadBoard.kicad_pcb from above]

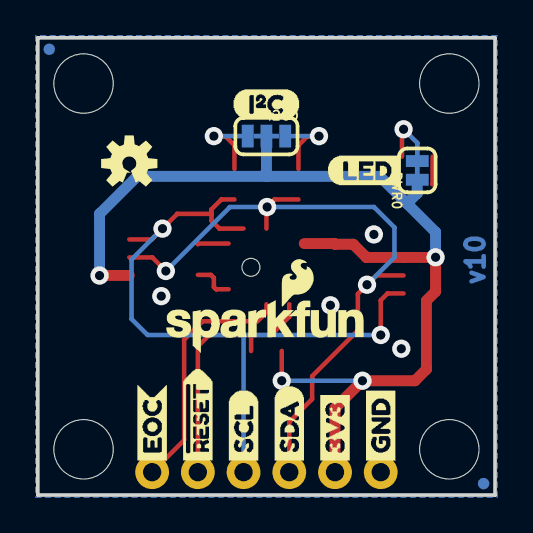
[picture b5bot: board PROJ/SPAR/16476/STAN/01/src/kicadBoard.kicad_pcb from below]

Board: 2 copper layers, 25.4 x 25.4 mm, 44 parts (14 on the bottom side), 12 nets.

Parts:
C1: 0.1uF; 0603
C2: 1nF; 0603
D1: RED; LED-0603
FD1, FD2, FD3, FD4: FIDUCIALUFIDUCIAL; FIDUCIAL-MICRO
FRAME1: FRAME-LETTER; CREATIVE_COMMONS
H1, H2, H3, H4: STAND-OFF
I2C0: SMT-JUMPER_3_2-NC_TRACE_SILK
J1, J2: Qwiic; JST04_1MM_RA
J3: 1X04_NO_SILK
J4: 1X02_NO_SILK
LOGO1: QWIIC_LOGO_5MM; QWIIC_5MM
LOGO2: OSHW-LOGOS; OSHW-LOGO-S
LOGO3: SFE_LOGO_NAME_FLAME.1_INCH; SFE_LOGO_NAME_FLAME_.1
PWR0: SMT-JUMPER_2_NC_TRACE_SILK
R1, R2, R4: 2.2k; 0603
R3: 1k; 0603
U1: MPR Series; MPR_SERIES_PRESSURE_I2C
U$1, U$15: GND1
U$2, U$14: 3V30
U$3, U$13: SDA2
U$4, U$12: SCL3
U$5, U$11: #RESET4
U$6, U$10: EOC5
U$7: PWR0
U$8: LED7
U$9: I#C0
U$16: QWIIC_MICROPRESSURE0
U$18: SENSOR2
U$19: SFE_LOGO_NAME_.1

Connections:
3.3V: C1.1, I2C0.2, J1.2, J2.2, J3.2, PWR0.1, R4.1, U1.12
EOC: J4.2, U1.8
GND: C1.2, D1.C, J1.1, J2.1, J3.1, U1.10
unnamed: PWR0.2, R3.2
unnamed: D1.A, R3.1
unnamed: I2C0.1, R2.2
unnamed: I2C0.3, R1.2
unnamed: C2.2, U1.4
unnamed: C2.1, U1.6
SCL: J1.4, J2.4, J3.4, R2.1, U1.3
SDA: J1.3, J2.3, J3.3, R1.1, U1.2
~RESET: J4.1, R4.2, U1.9

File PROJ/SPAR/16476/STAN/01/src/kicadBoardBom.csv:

"Id";"Designator";"Package";"Quantity";"Designation";"Supplier and ref";
1;"J2,J1";"JST04_1MM_RA";2;"Qwiic";;;
2;"U$4,U$12";"SCL3";2;"";;;
3;"U$5,U$11";"#RESET4";2;"";;;
4;"H1,H3,H2,H4";"STAND-OFF";4;"STAND-OFF";;;
5;"U$19";"SFE_LOGO_NAME_.1";1;"";;;
6;"FD1,FD4,FD2,FD3";"FIDUCIAL-MICRO";4;"FIDUCIALUFIDUCIAL";;;
7;"R3";"0603";1;"1k";;;
8;"J4";"1X02_NO_SILK";1;"";;;
9;"LOGO1";"QWIIC_5MM";1;"QWIIC_LOGO_5MM";;;
10;"U$16";"QWIIC_MICROPRESSURE0";1;"";;;
11;"U$1,U$15";"GND1";2;"";;;
12;"C2";"0603";1;"1nF";;;
13;"R1,R2,R4";"0603";3;"2.2k";;;
14;"U$6,U$10";"EOC5";2;"";;;
15;"J3";"1X04_NO_SILK";1;"";;;
16;"FRAME1";"CREATIVE_COMMONS";1;"FRAME-LETTER";;;
17;"U$7";"PWR0";1;"";;;
18;"U$2,U$14";"3V30";2;"";;;
19;"U1";"MPR_SERIES_PRESSURE_I2C";1;"MPR Series";;;
20;"D1";"LED-0603";1;"RED";;;
21;"U$18";"SENSOR2";1;"";;;
22;"C1";"0603";1;"0.1uF";;;
23;"U$3,U$13";"SDA2";2;"";;;
24;"I2C0";"SMT-JUMPER_3_2-NC_TRACE_SILK";1;"";;;
25;"PWR0";"SMT-JUMPER_2_NC_TRACE_SILK";1;"";;;
26;"U$8";"LED7";1;"";;;
27;"LOGO3";"SFE_LOGO_NAME_FLAME_.1";1;"SFE_LOGO_NAME_FLAME.1_INCH";;;
28;"LOGO2";"OSHW-LOGO-S";1;"OSHW-LOGOS";;;
29;"U$9";"I#C0";1;"";;;

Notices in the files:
parts and their libraries:
RELEASED UNDER THE CREATIVE COMMONS ATTRIBUTION SHARE-ALIKE 4.0 LICENSE
HTTPS://CREATIVECOMMONS.ORG/LICENSES/BY-SA/4.0
